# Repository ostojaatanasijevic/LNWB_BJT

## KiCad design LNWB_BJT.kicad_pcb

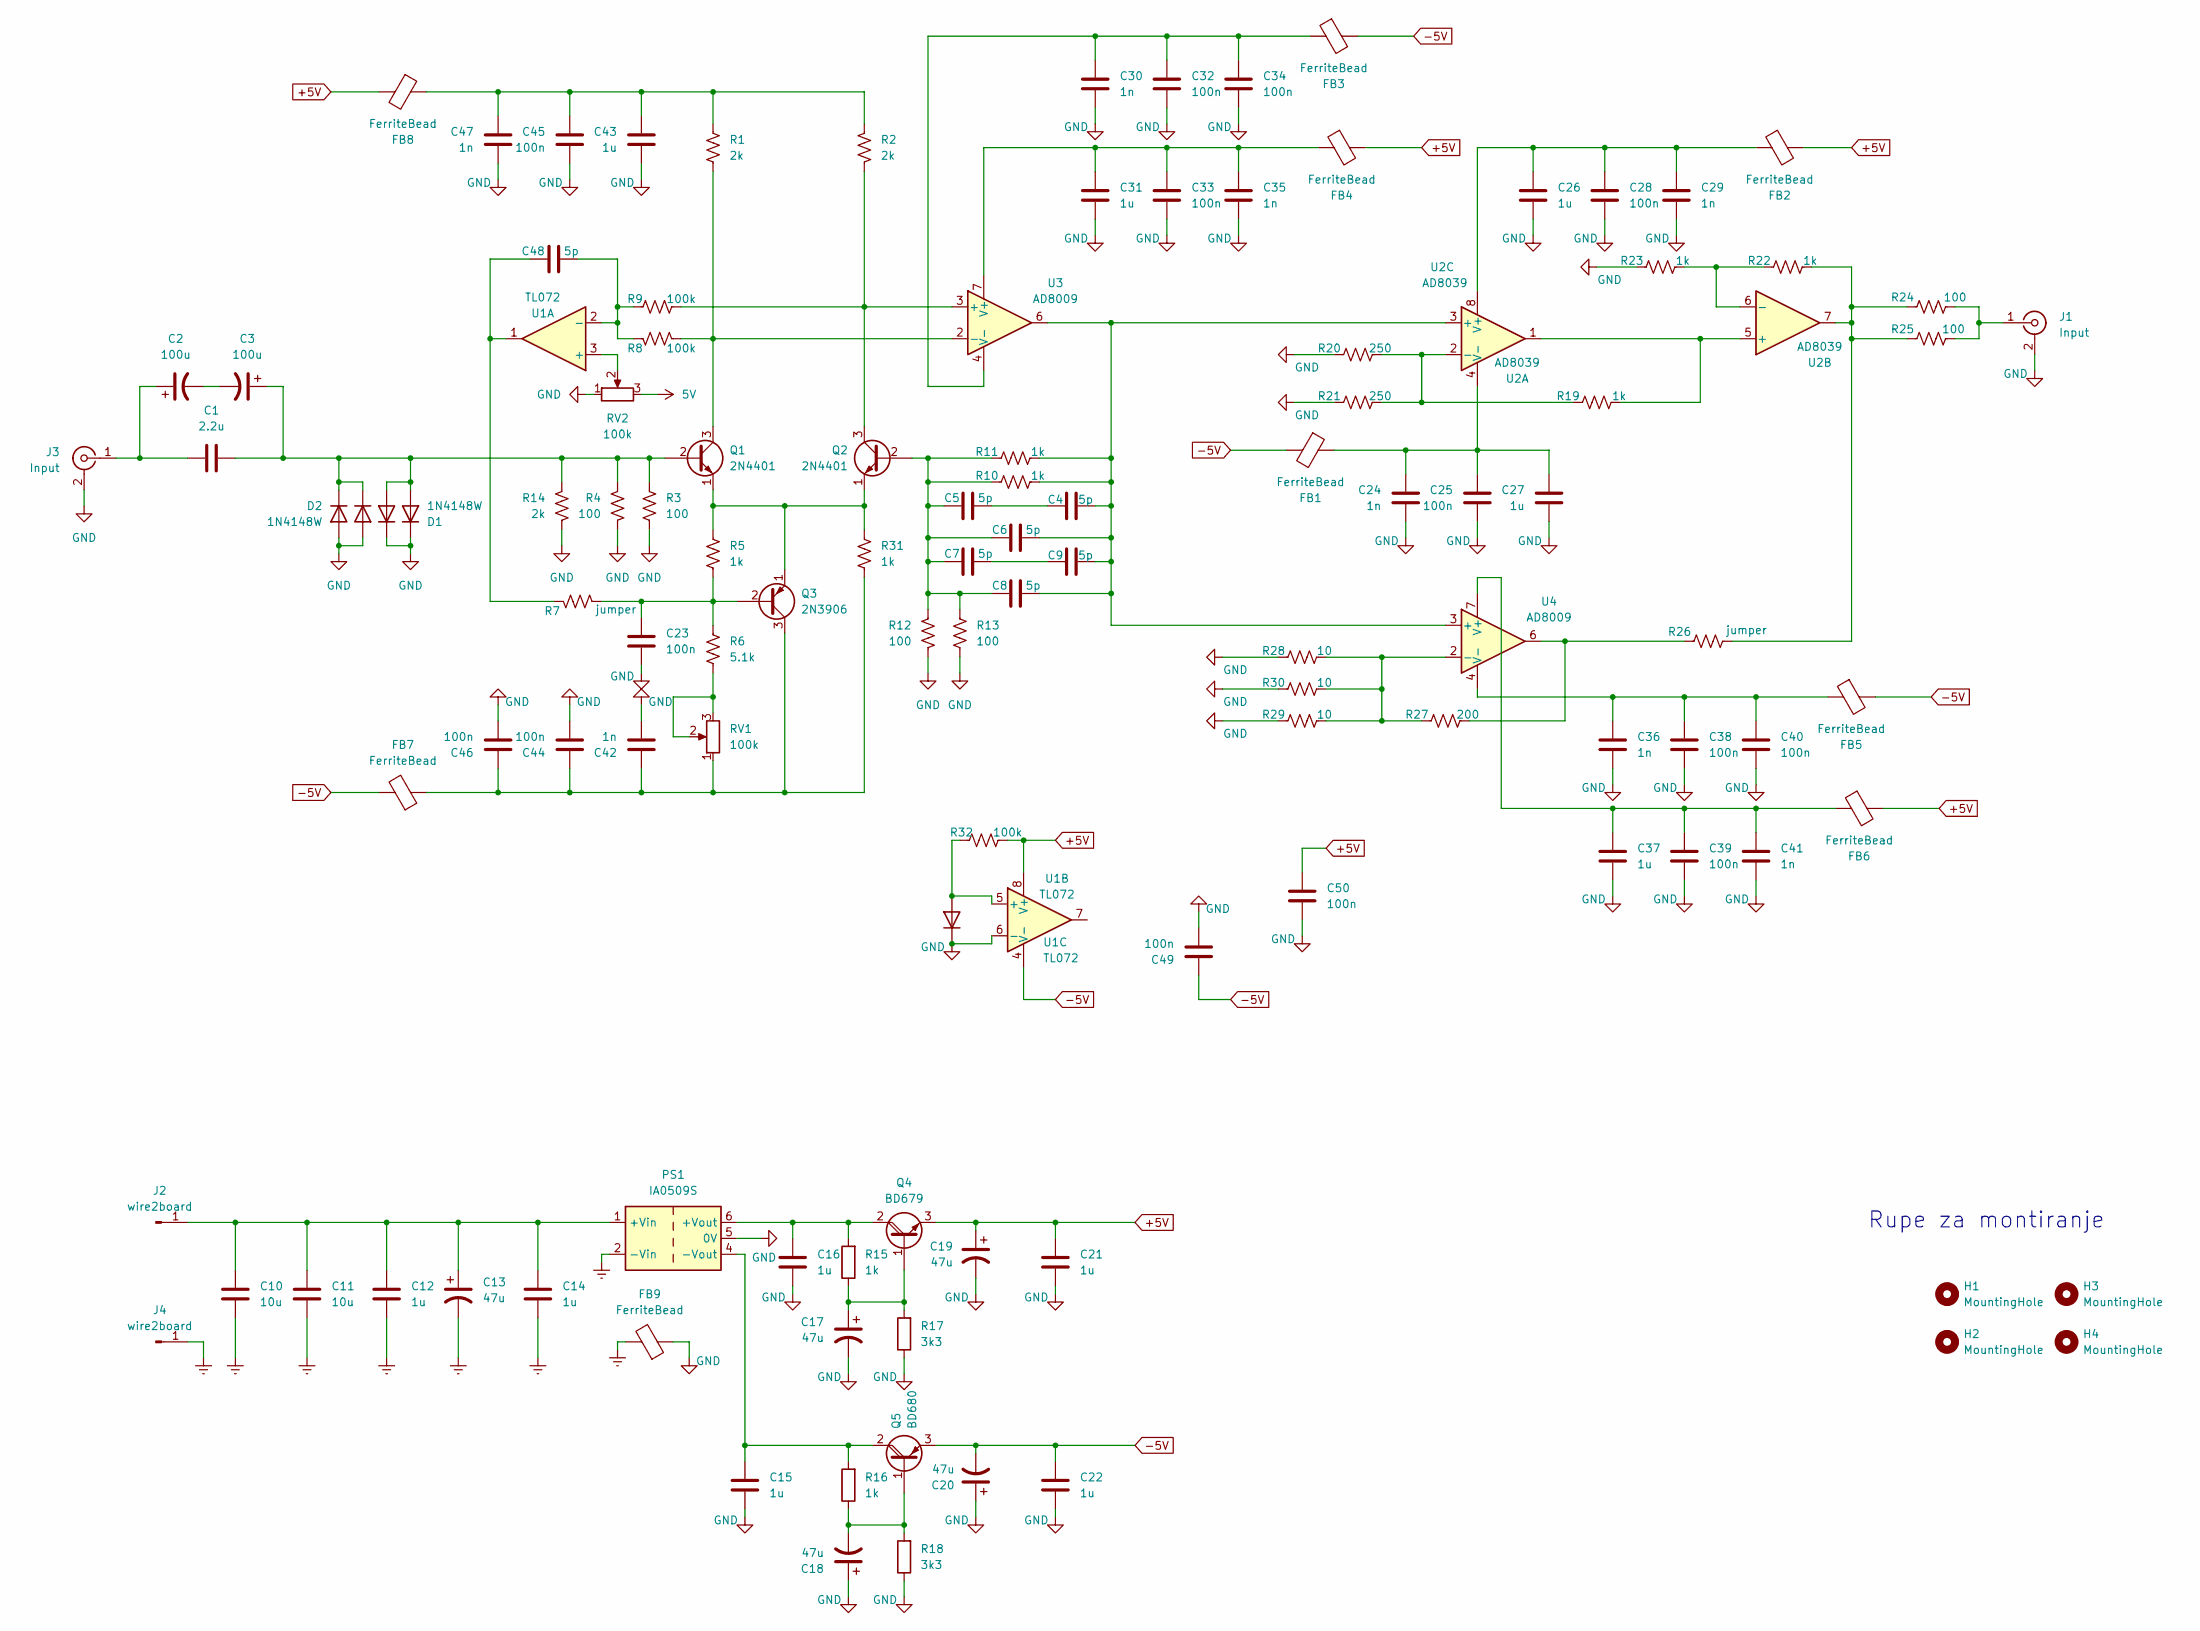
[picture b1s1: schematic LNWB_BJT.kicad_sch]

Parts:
C1: 2.2u; C_1206_3216Metric_Pad1.33x1.80mm_HandSolder
C2, C3: 100u; CP_Radial_D8.0mm_P3.50mm
C4, C5, C7, C9, C48: 5p; C_0603_1608Metric_Pad1.08x0.95mm_HandSolder
C6, C8: 5p; C_Disc_D5.0mm_W2.5mm_P2.50mm
C10, C11: 10u; R_1206_3216Metric_Pad1.30x1.75mm_HandSolder
C12, C14, C15, C16, C21, C22, C26, C27, C31, C37, C43: 1u; R_0603_1608Metric_Pad0.98x0.95mm_HandSolder
C13, C17, C18, C19, C20: 47u; CP_Radial_D5.0mm_P2.00mm
C23, C25, C28, C32, C33, C34, C38, C39, C40, C44, C45, C46, C49, C50: 100n; R_0603_1608Metric_Pad0.98x0.95mm_HandSolder
C24, C29, C30, C35, C36, C41, C42, C47: 1n; R_0603_1608Metric_Pad0.98x0.95mm_HandSolder
D1, D2: 1N4148W; D_0603_1608Metric_Pad1.05x0.95mm_HandSolder
D3, D4, D5: 1N4148; D_DO-35_SOD27_P7.62mm_Horizontal
FB1, FB2, FB3, FB4, FB5, FB6, FB7, FB8, FB9: FerriteBead; L_0603_1608Metric_Pad1.05x0.95mm_HandSolder
H1, H2, H3, H4: MountingHole; MountingHole_3.2mm_M3_ISO14580_Pad_TopBottom
J1, J3: Input; BNC_Amphenol_B6252HB-NPP3G-50_Horizontal
J2, J4: wire2board; SolderWire-0.25sqmm_1x01_D0.65mm_OD1.7mm
PS1: IA0509S; Converter_DCDC_XP_POWER-IAxxxxS_THT
Q1, Q2: 2N4401; TO-92_Inline
Q3: 2N3906; TO-92_Inline
Q4: BD679; TO-126-3_Horizontal_TabUp
Q5: BD680; TO-126-3_Horizontal_TabUp
R1, R2, R14: 2k; R_0603_1608Metric_Pad0.98x0.95mm_HandSolder
R3, R4, R12, R13, R24, R25: 100; R_0603_1608Metric_Pad0.98x0.95mm_HandSolder
R5, R10, R11, R15, R16, R19, R22, R23, R31: 1k; R_0603_1608Metric_Pad0.98x0.95mm_HandSolder
R6: 5.1k; R_0603_1608Metric_Pad0.98x0.95mm_HandSolder
R7, R26: jumper; R_0603_1608Metric_Pad0.98x0.95mm_HandSolder
R8, R9, R32: 100k; R_0603_1608Metric_Pad0.98x0.95mm_HandSolder
R17, R18: 3k3; R_0603_1608Metric_Pad0.98x0.95mm_HandSolder
R20, R21: 250; R_0603_1608Metric_Pad0.98x0.95mm_HandSolder
R27: 200; R_0603_1608Metric_Pad0.98x0.95mm_HandSolder
R28, R29, R30: 10; R_0603_1608Metric_Pad0.98x0.95mm_HandSolder
RV1, RV2: 100k; Potentiometer_Bourns_3296W_Vertical
U1: TL072; SOIC-8_3.9x4.9mm_P1.27mm
U2: AD8039; SOIC-8_3.9x4.9mm_P1.27mm
U3, U4: AD8009; SOIC-8_3.9x4.9mm_P1.27mm

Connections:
5V: RV2.3
+5V: C19.1, C21.1, C50.2, FB2.2, FB4.2, FB6.2, FB8.2, Q4.3 (E), R32.2, U1.8 (V+)
-5V: C20.2, C22.1, C49.2, FB1.2, FB3.2, FB5.2, FB7.2, Q5.3 (E), U1.4 (V-)
Earth: C10.1, C11.1, C12.1, C13.2, C14.2, FB9.2, J4.1, PS1.2 (-Vin)
GND: C15.2, C16.2, C17.2, C18.1, C19.2, C20.1, C21.2, C22.2, C23.2, C24.1, C25.1, C26.1, C27.1, C28.1, C29.1, C30.1, C31.1, C32.1, C33.1, C34.1, C35.1, C36.1, C37.1, C38.1, C39.1, C40.1, C41.1, C42.1, C43.1, C44.1, C45.1, C46.1, C47.1, C49.1, C50.1, D1.1 (K), D2.2 (A), D3.2 (A), D4.1 (K), D5.1 (K), FB9.1, J1.2 (Ext), J3.2 (Ext), PS1.5 (0V), R3.2, R4.2, R12.2, R13.2, R14.2, R17.1, R18.1, R20.1, R21.1, R23.1, R28.1, R29.1, R30.1, RV2.1, U1.6 (-)
unnamed: C2.2, C3.2
unnamed: C4.1, C5.2
unnamed: C7.2, C9.1
unnamed: C43.2, C45.2, C47.2, FB8.1, R1.1, R2.1
unnamed: C48.1, R7.1, U1.1
unnamed: C1.2, C3.1, D1.2 (A), D2.1 (K), D3.1 (K), D4.2 (A), Q1.2 (B), R3.1, R4.1, R14.1
unnamed: D5.2 (A), R32.1, U1.5 (+)
unnamed: J1.1 (In), R24.2, R25.2
unnamed: C10.2, C11.2, C12.2, C13.1, C14.1, J2.1, PS1.1 (+Vin)
unnamed: C1.1, C2.1, J3.1 (In)
unnamed: C16.1, PS1.6 (+Vout), Q4.2 (C), R15.2
unnamed: C15.1, PS1.4 (-Vout), Q5.2 (C), R16.2
unnamed: Q1.3 (C), R1.2, R8.2, U3.2 (-)
unnamed: Q1.1 (E), Q2.1 (E), Q3.1 (E), R5.1, R31.1
unnamed: C5.1, C6.1, C7.1, C8.1, Q2.2 (B), R10.1, R11.1, R12.1, R13.1
unnamed: Q2.3 (C), R2.2, R9.2, U3.3 (+)
unnamed: C23.1, Q3.2 (B), R5.2, R6.1, R7.2
unnamed: C42.2, C44.2, C46.2, FB7.1, Q3.3 (C), R31.2, RV1.1
unnamed: C17.1, Q4.1 (B), R15.1, R17.2
unnamed: C18.2, Q5.1 (B), R16.1, R18.2
unnamed: R6.2, RV1.2, RV1.3
unnamed: R22.2, R24.1, R25.1, R26.2, U2.7
unnamed: R26.1, R27.2, U4.6
unnamed: RV2.2, U1.3 (+)
unnamed: C48.2, R8.1, R9.1, U1.2 (-)
unnamed: C4.2, C6.2, C8.2, C9.2, R10.2, R11.2, U2.3 (+), U3.6, U4.3 (+)
unnamed: R19.1, R20.2, R21.2, U2.2 (-)
unnamed: R19.2, U2.1, U2.5 (+)
unnamed: R22.1, R23.2, U2.6 (-)
unnamed: C26.2, C28.2, C29.2, FB2.1, U2.8 (V+)
unnamed: C24.2, C25.2, C27.2, FB1.1, U2.4 (V-)
unnamed: C31.2, C33.2, C35.2, FB4.1, U3.7 (V+)
unnamed: C30.2, C32.2, C34.2, FB3.1, U3.4 (V-)
unnamed: R27.1, R28.2, R29.2, R30.2, U4.2 (-)
unnamed: C37.2, C39.2, C41.2, FB6.1, U4.7 (V+)
unnamed: C36.2, C38.2, C40.2, FB5.1, U4.4 (V-)

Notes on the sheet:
Rupe za montiranje

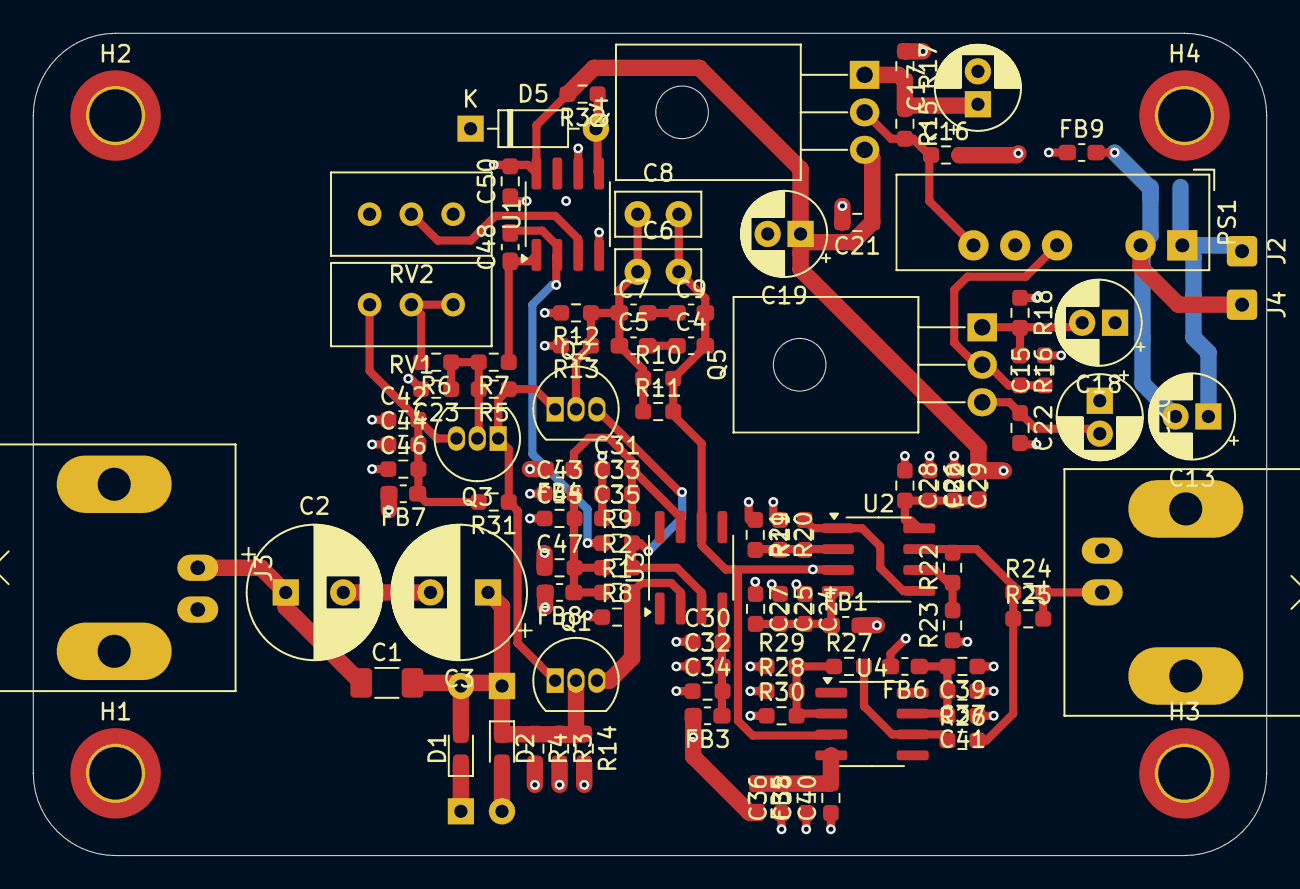
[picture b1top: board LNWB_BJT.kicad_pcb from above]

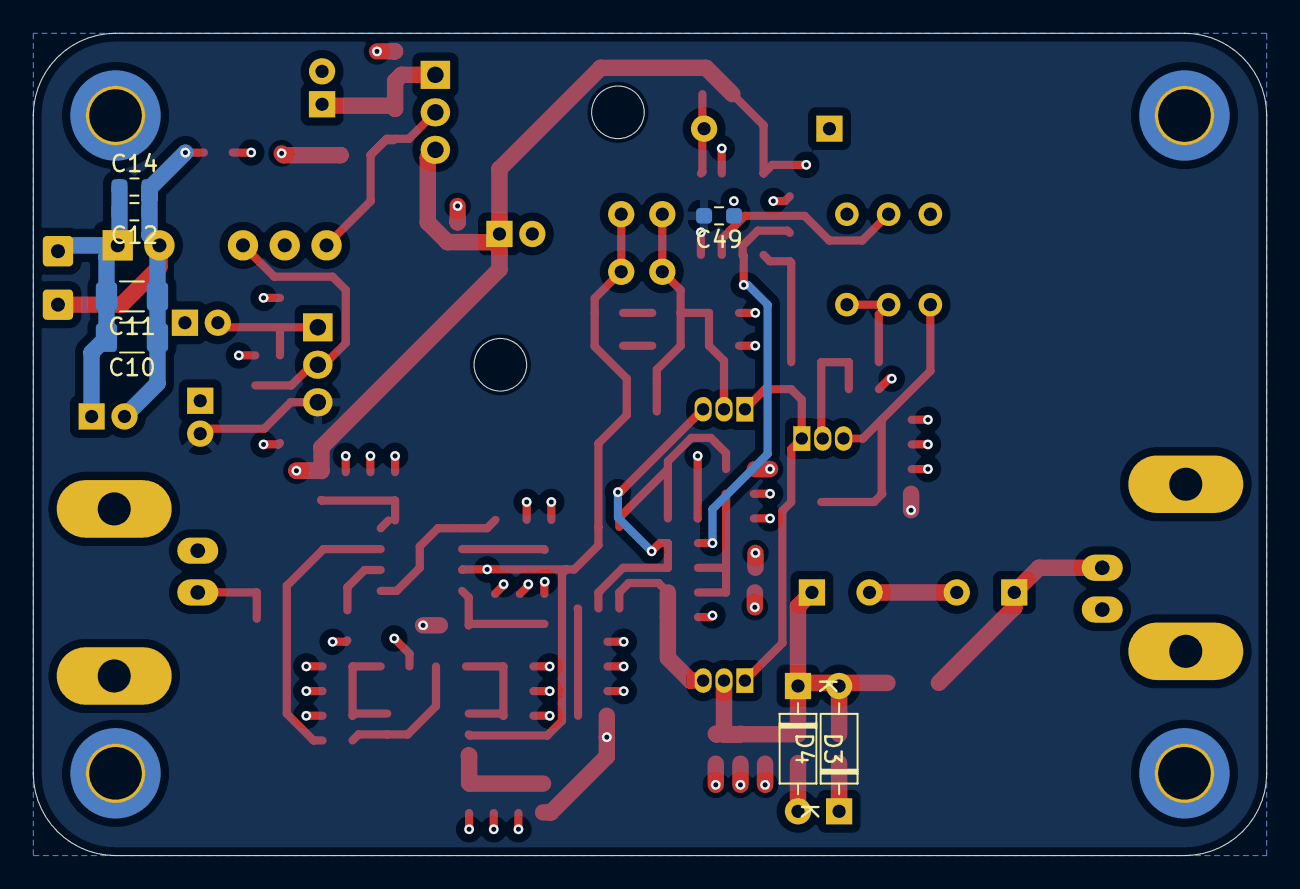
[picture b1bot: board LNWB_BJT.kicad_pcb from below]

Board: 4 copper layers, 75.0 x 50.0 mm, 116 parts (7 on the bottom side), 40 nets.

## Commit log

2024-12-12 Init.
2024-12-12 RM npy.
2024-12-12 Mounting holes, edge cuts.
2024-12-12 klfdsa.wq
2024-12-14 send.
2024-12-14 PCB.
